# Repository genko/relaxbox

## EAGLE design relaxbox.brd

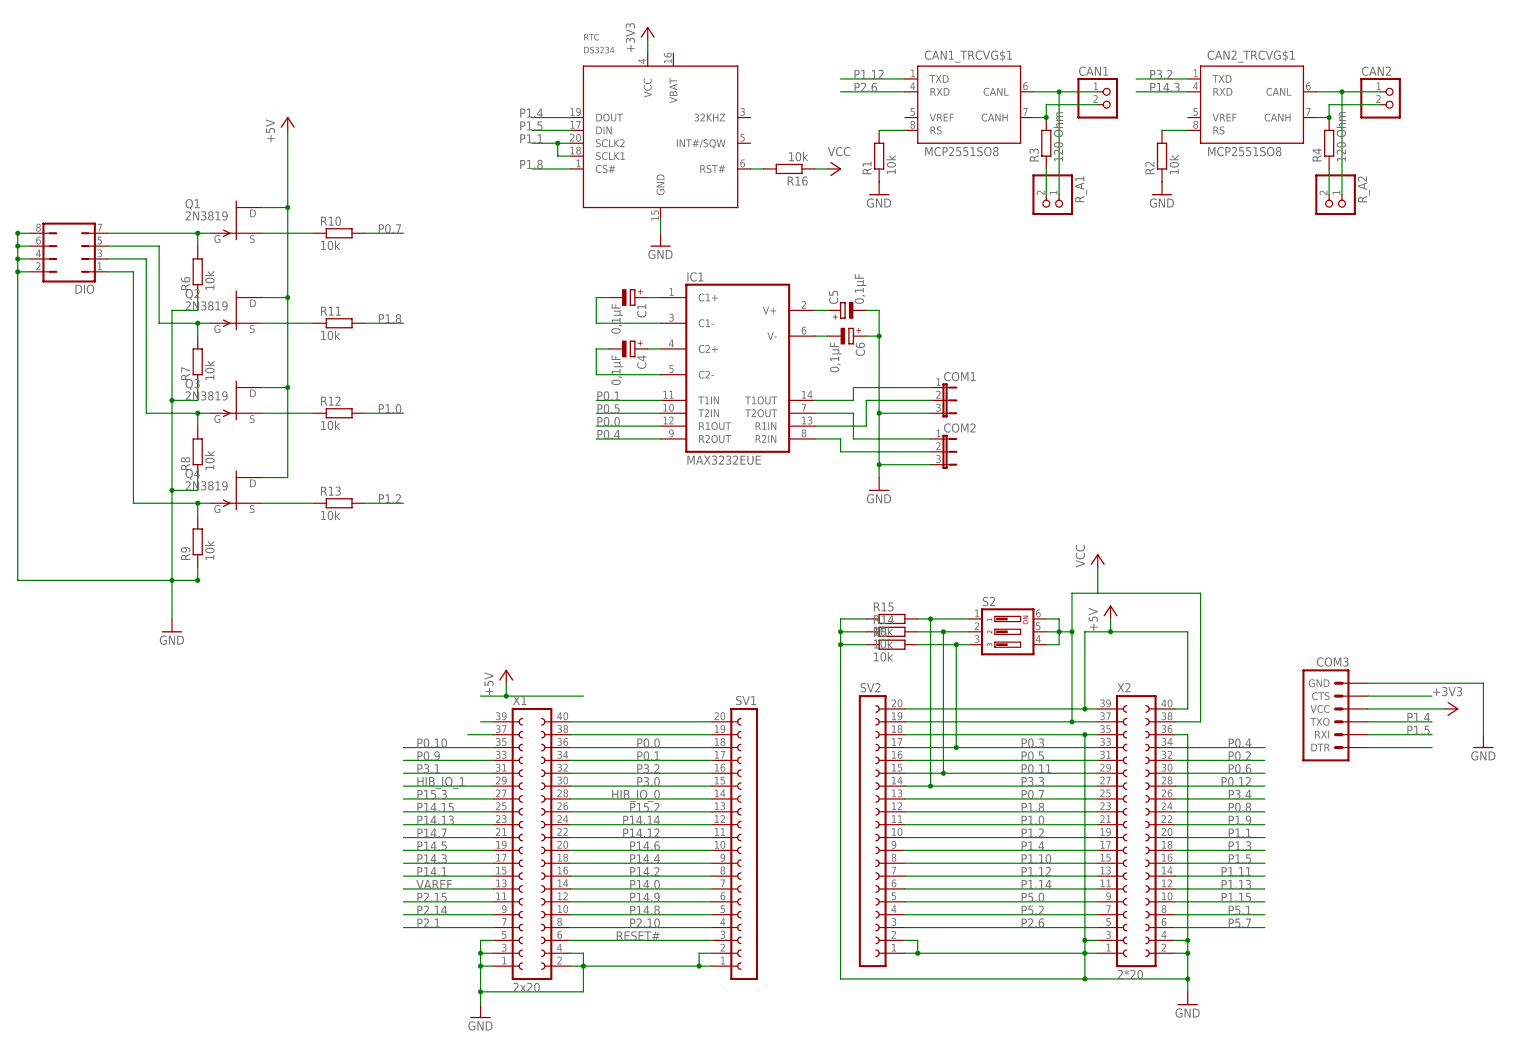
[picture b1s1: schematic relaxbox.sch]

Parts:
C1, C4, C5, C6: 0,1µF; E2,5-5
CAN1, CAN2: PINHD-1X2; 1X02
CAN1_TRCV, CAN2_TRCV: MCP2551SO8; SO08
COM1, COM2: JP2E; JP2
COM3: SPARKFUN_ARDUINO_SERIAL_PROGRAMPTH; SPARKFUN_1X06
DIO: JP4Q
IC1: MAX3232EUE; TSSOP16
Q1, Q2, Q3, Q4: 2N3819; TO92
R1, R2, R5, R6, R7, R8, R9, R10, R11, R12, R13, R14, R15, R16: 10k; M0805
R3, R4: 120 Ohm; M0805
RTC: DS3234; SO-20DW
R_A1, R_A2: PINHD-1X2; 1X02
S2: DIP03YL
SV1, SV2: FE20-1; FE20
X1: 2x20; FE20-2
X2: 2*20; FE20-2

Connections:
+3V3: COM3.4 (VCC), RTC.4 (VCC)
+5V: Q1.1 (D), Q2.1 (D), Q3.1 (D), Q4.1 (D), SV2.20, X2.39, X2.40
CANH1: CAN1.2, CAN1_TRCV.7 (CANH), R3.2
CANH2: CAN2.2, CAN2_TRCV.7 (CANH), R4.2
CANL1: CAN1.1, CAN1_TRCV.6 (CANL), R_A1.1
CANL2: CAN2.1, CAN2_TRCV.6 (CANL), R_A2.1
GND: C5.-, C6.+, CAN1_TRCV.2 (GND), CAN2_TRCV.2 (GND), COM1.3, COM2.3, COM3.6 (GND), DIO.2, DIO.4, DIO.6, DIO.8, IC1.15 (GND), R1.1, R2.1, R5.1, R6.1, R7.1, R8.1, R9.1, R14.1, R15.1, RTC.15 (GND), SV1.1, SV1.2, SV2.1, SV2.2, SV2.18, X1.1, X1.2, X1.3, X1.4, X1.5, X2.1, X2.2, X2.3, X2.4, X2.35, X2.36
HIB_IO_0: SV1.14, X1.28
HIB_IO_1: X1.29
unnamed: SV1.20, X1.40
unnamed: SV1.19, X1.38
unnamed: C1.+, IC1.1 (C1+)
unnamed: C1.-, IC1.3 (C1-)
unnamed: R16.2, RTC.6 (RST#)
unnamed: C4.+, IC1.4 (C2+)
unnamed: C4.-, IC1.5 (C2-)
unnamed: CAN1_TRCV.8 (RS), R1.2
unnamed: CAN2_TRCV.8 (RS), R2.2
unnamed: C5.+, IC1.2 (V+)
unnamed: C6.-, IC1.6 (V-)
unnamed: R3.1, R_A1.2
unnamed: R4.1, R_A2.2
unnamed: DIO.7, Q1.2 (G), R6.2
unnamed: Q1.3 (S), R10.1
unnamed: DIO.1, Q4.2 (G), R9.2
unnamed: DIO.3, Q3.2 (G), R8.2
unnamed: DIO.5, Q2.2 (G), R7.2
unnamed: Q2.3 (S), R11.1
unnamed: Q3.3 (S), R12.1
unnamed: Q4.3 (S), R13.1
unnamed: COM1.1, IC1.14 (T1OUT)
unnamed: COM1.2, IC1.13 (R1IN)
unnamed: COM2.1, IC1.7 (T2OUT)
unnamed: COM2.2, IC1.8 (R2IN)
P0.0: IC1.12 (R1OUT), SV1.18, X1.36
P0.1: IC1.11 (T1IN), SV1.17, X1.34
P0.2: X2.32
P0.3: R5.2, S2.3, SV2.17, X2.33
P0.4: IC1.9 (R2OUT), X2.34
P0.5: IC1.10 (T2IN), SV2.16, X2.31
P0.6: X2.30
P0.7: R10.2, SV2.13, X2.25
P0.8: X2.24
P0.9: X1.33
P0.10: X1.35
P0.11: R14.2, S2.2, SV2.15, X2.29
P0.12: X2.28
P1.0: R12.2, SV2.11, X2.21
P1.1: RTC.18 (SCLK1), RTC.20 (SCLK2), X2.20
P1.2: R13.2, SV2.10, X2.19
P1.3: X2.18
P1.4: COM3.3 (TXO), RTC.19 (DOUT), SV2.9, X2.17
P1.5: COM3.2 (RXI), RTC.17 (DIN), X2.16
P1.8: R11.2, RTC.1 (CS#), SV2.12, X2.23
P1.9: X2.22
P1.10: SV2.8, X2.15
P1.11: X2.14
P1.12: CAN1_TRCV.1 (TXD), SV2.7, X2.13
P1.13: X2.12
P1.14: SV2.6, X2.11
P1.15: X2.10
P2.1: X1.7
P2.6: CAN1_TRCV.4 (RXD), SV2.3, X2.5
P2.10: SV1.4, X1.8
P2.14: X1.9
P2.15: X1.11
P3.0: SV1.15, X1.30
P3.1: X1.31
P3.2: CAN2_TRCV.1 (TXD), SV1.16, X1.32
P3.3: R15.2, S2.1, SV2.14, X2.27
P3.4: X2.26
P5.0: SV2.5, X2.9
P5.1: X2.8
P5.2: SV2.4, X2.7
P5.7: X2.6
P14.0: SV1.7, X1.14
P14.1: X1.15
P14.2: SV1.8, X1.16
P14.3: CAN2_TRCV.4 (RXD), X1.17
P14.4: SV1.9, X1.18
P14.5: X1.19
P14.6: SV1.10, X1.20
P14.7: X1.21
P14.8: SV1.5, X1.10
P14.9: SV1.6, X1.12
P14.12: SV1.11, X1.22
P14.13: X1.23
P14.14: SV1.12, X1.24
P14.15: X1.25
P15.2: SV1.13, X1.26
P15.3: X1.27
RESET#: SV1.3, X1.6
VAREF: X1.13
VCC: CAN1_TRCV.3 (VCC), CAN2_TRCV.3 (VCC), IC1.16 (VCC), R16.1, S2.4, S2.5, S2.6, SV2.19, X2.37, X2.38

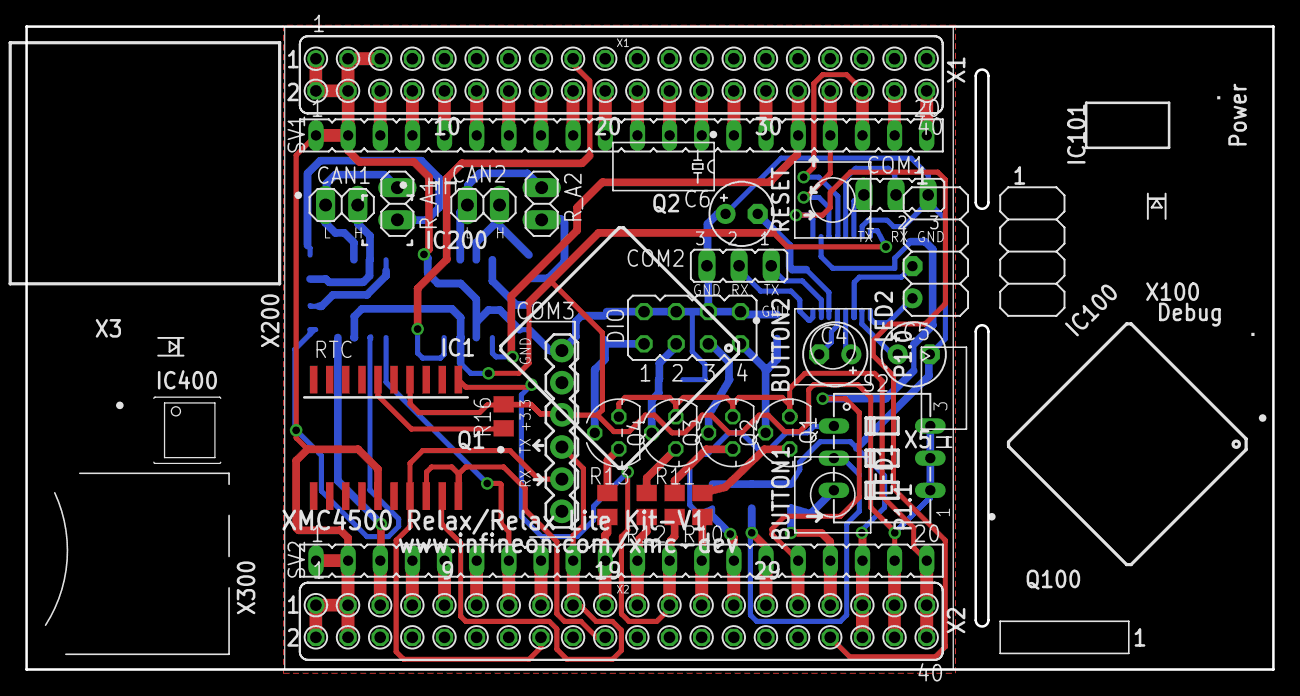
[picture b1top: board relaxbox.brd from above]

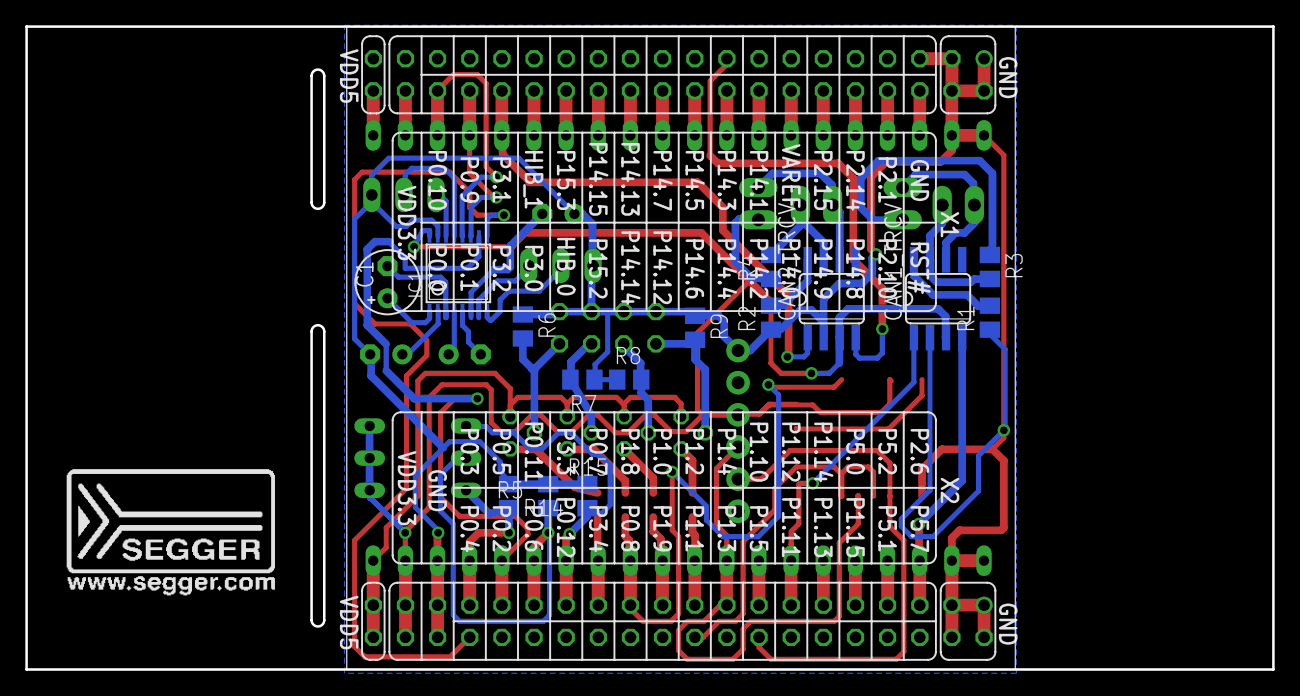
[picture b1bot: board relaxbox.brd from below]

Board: 2 copper layers, 98.5 x 50.8 mm, 41 parts (15 on the bottom side), 68 nets.

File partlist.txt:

Partlist

Exported from relaxbox.sch at 09.05.13 23:41

EAGLE Version 6.4.0 Copyright (c) 1988-2013 CadSoft

Assembly variant: 

Part     Value          Device                             Package       Library                 Sheet	Reichelt-No			Farnell-No

C1       0,1µF          CPOL-EUE2.5-5                      E2,5-5        rcl                     1	RAD 0,1/100	0,04 ¤
C4       0,1µF          CPOL-EUE2.5-5                      E2,5-5        rcl                     1	RAD 0,1/100	0,04 ¤
C5       0,1µF          CPOL-EUE2.5-5                      E2,5-5        rcl                     1	RAD 0,1/100	0,04 ¤
C6       0,1µF          CPOL-EUE2.5-5                      E2,5-5        rcl                     1	RAD 0,1/100	0,04 ¤
CAN1                    PINHD-1X2                          1X02          pinhead                 1	MPE 087-1-002	0,05 ¤
CAN2                    PINHD-1X2                          1X02          pinhead                 1	MPE 087-1-002	0,05 ¤
COM1                    JP2E                               JP2           jumper                  1	MPE 087-1-003	0,08 ¤
COM2                    JP2E                               JP2           jumper                  1	MPE 087-1-003	0,08 ¤
COM3                    SPARKFUN_ARDUINO_SERIAL_PROGRAMPTH SPARKFUN_1X06 ArduinoBluetoothMatev13 1	MPE 087-1-006	0,15 ¤
DIO                     JP4Q                               JP4Q          jumper                  1	MPE 094-2-008	0,28 ¤
IC1      MAX3232EUE     MAX3232EUE                         TSSOP16       maxim                   1					1460372	  1,78¤
Q1       2N3819         2N3819                             TO92          transistor-fet          1	2N 3819		0,35 ¤
Q2       2N3819         2N3819                             TO92          transistor-fet          1	2N 3819		0,35 ¤
Q3       2N3819         2N3819                             TO92          transistor-fet          1	2N 3819		0,35 ¤
Q4       2N3819         2N3819                             TO92          transistor-fet          1	2N 3819		0,35 ¤
R1       10k            R-EU_M0805                         M0805         rcl                     1	SMD-0805 10,0K	0,082 ¤
R2       10k            R-EU_M0805                         M0805         rcl                     1	SMD-0805 10,0K	0,082 ¤
R3       120 Ohm        R-EU_M0805                         M0805         rcl                     1	SMD-0805 120	0,103 ¤	
R4       120 Ohm        R-EU_M0805                         M0805         rcl                     1	SMD-0805 120	0,103 ¤
R5       10k            R-EU_M0805                         M0805         rcl                     1	SMD-0805 10,0K	0,082 ¤
R6       10k            R-EU_M0805                         M0805         rcl                     1	SMD-0805 10,0K	0,082 ¤
R7       10k            R-EU_M0805                         M0805         rcl                     1	SMD-0805 10,0K	0,082 ¤
R8       10k            R-EU_M0805                         M0805         rcl                     1	SMD-0805 10,0K	0,082 ¤
R9       10k            R-EU_M0805                         M0805         rcl                     1	SMD-0805 10,0K	0,082 ¤
R10      10k            R-EU_M0805                         M0805         rcl                     1	SMD-0805 10,0K	0,082 ¤
R11      10k            R-EU_M0805                         M0805         rcl                     1	SMD-0805 10,0K	0,082 ¤
R12      10k            R-EU_M0805                         M0805         rcl                     1	SMD-0805 10,0K	0,082 ¤
R13      10k            R-EU_M0805                         M0805         rcl                     1	SMD-0805 10,0K	0,082 ¤
R14      10k            R-EU_M0805                         M0805         rcl                     1	SMD-0805 10,0K	0,082 ¤
R15      10k            R-EU_M0805                         M0805         rcl                     1	SMD-0805 10,0K	0,082 ¤
R16      10k            R-EU_M0805                         M0805         rcl                     1	SMD-0805 10,0K	0,082 ¤
RTC      DS3234         DS3234                             SO-20DW       ds3234                  1
R_A1                    PINHD-1X2                          1X02          pinhead                 1	MPE 087-1-002	0,050 ¤
R_A2                    PINHD-1X2                          1X02          pinhead                 1	MPE 087-1-002	0,050 ¤
S2                      DIP03YL                            DIP03YL       switch-dil              1	NT 03		0,33 ¤
SV1                     FE20-1                             FE20          con-lsta                1	BL 1X20G7 2,54	0,91 ¤ (Präz Buchsenleiste)
SV2                     FE20-1                             FE20          con-lsta                1	BL 1X20G7 2,54	0,91 ¤ (Präz Buchsenleiste)
U$1      MCP2551SO8     MCP2551SO8                         SO08          can                     1	MCP 2551-I/SN	1,10 ¤
U$3      MCP2551SO8     MCP2551SO8                         SO08          can                     1	MCP 2551-I/SN	1,10 ¤
X1       2x20           FE20-2                             FE20-2        con-lsta                1	BL 2X10G8 2,54	0,30 ¤ (2x10 pins Standard)
X2       2*20           FE20-2                             FE20-2        con-lsta                1	BL 2X10G8 2,54	0,30 ¤ (2x10 pins Standard)

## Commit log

2013-03-15 Initial commit!
2013-03-15 Adding UARTS from david
2013-03-26 Schematic erweitert + Board placement
2013-03-29 Library of Arduino Bluteooth module
2013-04-09 Added PinAssignment of usable UART and CAN pins.
2013-04-09 Entfernen von bereits verwendetem PIN aus CAN-Auswahl.
2013-04-11 Erster Routing Versuch. Um neue Verbindungen hinzuzufügen, einfach im Schematic hinzufügen und im Board Ratsnest ausführen.
2013-04-19 Added SPI and CAN PINs.
2013-04-20 Fixed pin assignment for SPI
2013-04-21 Routed.
2013-04-21 Optimized routing.
2013-04-21 Optimized DRC settings.
2013-04-22 Fixed pin assignment.
2013-04-25 Final list of Pin Assignment.
2013-04-25 Changed Pin Assignment as it is not possible to run 4 USICs simultaneously.
2013-04-25 Changed tPlace labels
2013-04-27 Finish. Major change: COM1, COM2, COM3 had swapped RX and TX pins. --> fixed.
2013-04-27 finished.
2013-05-09 Teileliste und Bestellliste für Reichelt und Farnell
2013-05-13 Meine Bestellung hinzugefügt
2013-06-30 Bugfix. VDD and 3,3V net were not connected. So the power supply of the CAN tranceivers and the MAX3232 were not connected to the 3,3V supply
